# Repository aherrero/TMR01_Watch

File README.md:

# TMR01_Watch
Digital homemade wrist watch - Bora Watch

https://aherrero.github.io/atmega328/rtc/clock/diy/2018/11/29/BoraWatchv2.html

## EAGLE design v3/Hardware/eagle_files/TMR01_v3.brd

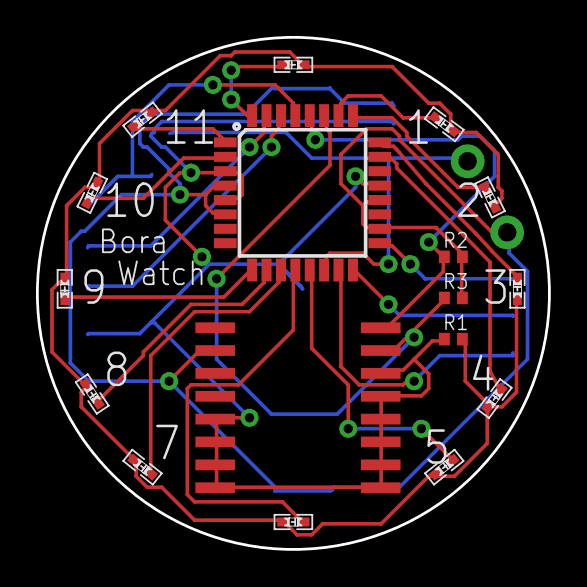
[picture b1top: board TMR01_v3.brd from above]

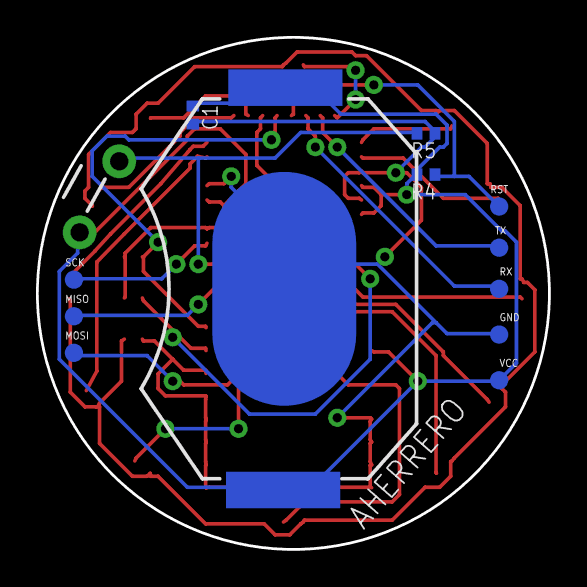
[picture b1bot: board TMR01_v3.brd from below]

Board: 2 copper layers, 28.4 x 28.4 mm, 30 parts (13 on the bottom side), 24 nets.

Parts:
BT1: BATTCON_20MM_4LEGS
C1: 100nF; 0402
D1, D2, D3, D4, D5, D6, D7, D8, D9, D10, D11, D12: 0402.LED
IC1: DS3231/SO; SO16W
R1: 470; 0402
R2, R3, R4, R5: 10k; 0402
S1: MOMENTARY-SWITCH-SPST; TACTILE_SWITCH_PTH_2_AHE
TP3, TP4, TP7, TP8, TP9, TP10, TP11, TP12: TEST-POINT3X4; PAD.03X.04
U1: ATMEGA328P_TQFP; TQFP32-08

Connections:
D1: D1.P$1, U1.26
D2: D2.P$1, U1.25
D3: D3.P$1, U1.24
D4: D4.P$1, U1.23
D5: D5.P$1, U1.13
D6: D6.P$1, U1.12
D7: D7.P$1, U1.11
D8: D8.P$1, U1.10
D9: D9.P$1, U1.9
D10: D10.P$1, U1.2
D11: D11.P$1, U1.1
D12: D12.P$1, U1.32
GND: BT1.NEGATIVE, C1.2, IC1.5, IC1.6, IC1.7, IC1.8, IC1.9, IC1.10, IC1.11, IC1.12, IC1.13, IC1.14, R1.1, R5.1, TP12.P$1, U1.3, U1.5, U1.21
MISO: TP7.P$1, U1.16
MOSI: TP10.P$1, U1.15
unnamed: D1.P$2, D2.P$2, D3.P$2, D4.P$2, D5.P$2, D6.P$2, D7.P$2, D8.P$2, D9.P$2, D10.P$2, D11.P$2, D12.P$2, R1.2
RST: R4.1, TP11.P$1, U1.29
RX: TP3.P$1, U1.30
SCK: TP9.P$1, U1.17
SCL: IC1.16, R2.1, U1.28
SDA: IC1.15, R3.1, U1.27
SS: R5.2, S1.2, U1.14
TX: TP4.P$1, U1.31
VCC: BT1.POSITIVE@1, BT1.POSITIVE@2, BT1.POSITIVE@3, BT1.POSITIVE@4, C1.1, IC1.2, R2.2, R3.2, R4.2, S1.1, TP8.P$1, U1.4, U1.6, U1.18, U1.20

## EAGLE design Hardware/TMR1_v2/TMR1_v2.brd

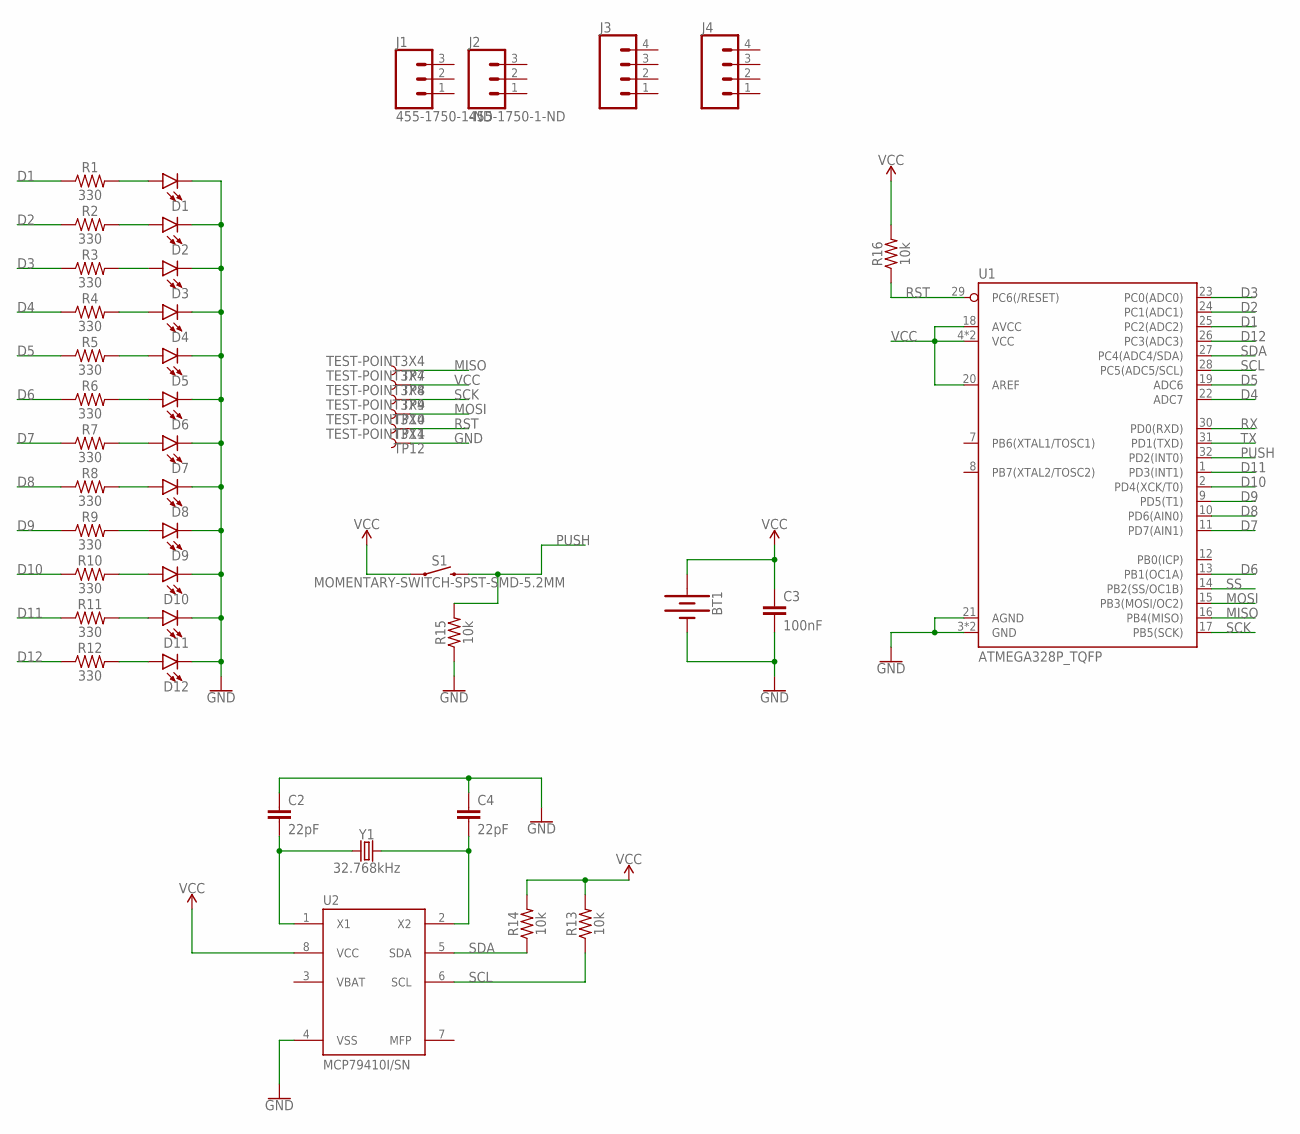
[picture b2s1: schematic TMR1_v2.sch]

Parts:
BT1: BATTERY-20MM_SMD_4LEGS; BATTCON_20MM_4LEGS
C2, C4: 22pF; 0603
C3: 100nF; 0603
D1, D2, D3, D4, D5, D6, D7, D8, D9, D10, D11, D12: LED0603; LED-0603
J1, J2: 455-1750-1-ND; 1X03
J3, J4: CONN_04; 1X04
R1, R2, R3, R4, R5, R6, R7, R8, R9, R10, R11, R12: 330; 0603
R13, R14, R15, R16: 10k; 0603
S1: MOMENTARY-SWITCH-SPST-SMD-5.2MM; TACTILE_SWITCH_SMD_5.2MM
TP7, TP8, TP9, TP10, TP11, TP12: TEST-POINT3X4; PAD.03X.04
U1: ATMEGA328P_TQFP; TQFP32-08
U2: MCP79410I/SN; SO8
Y1: 32.768kHz; CRYSTAL-SMD-MC-146

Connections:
D1: R1.1, U1.25 (PC2(ADC2))
D2: R2.1, U1.24 (PC1(ADC1))
D3: R3.1, U1.23 (PC0(ADC0))
D4: R4.1, U1.22 (ADC7)
D5: R5.1, U1.19 (ADC6)
D6: R6.1, U1.13 (PB1(OC1A))
D7: R7.1, U1.11 (PD7(AIN1))
D8: R8.1, U1.10 (PD6(AIN0))
D9: R9.1, U1.9 (PD5(T1))
D10: R10.1, U1.2 (PD4(XCK/T0))
D11: R11.1, U1.1 (PD3(INT1))
D12: R12.1, U1.26 (PC3(ADC3))
GND: BT1.NEGATIVE (-), C2.1, C3.2, C4.1, D1.C, D2.C, D3.C, D4.C, D5.C, D6.C, D7.C, D8.C, D9.C, D10.C, D11.C, D12.C, R15.1, TP12.P$1, U1.3 (GND), U1.5 (GND), U1.21 (AGND), U2.4 (VSS)
MISO: TP7.P$1, U1.16 (PB4(MISO))
MOSI: TP10.P$1, U1.15 (PB3(MOSI/OC2))
unnamed: D8.A, R8.2
unnamed: D7.A, R7.2
unnamed: D6.A, R6.2
unnamed: D5.A, R5.2
unnamed: D4.A, R4.2
unnamed: D3.A, R3.2
unnamed: D2.A, R2.2
unnamed: D1.A, R1.2
unnamed: C2.2, U2.1 (X1), Y1.P$2 (1)
unnamed: C4.2, U2.2 (X2), Y1.P$1 (2)
unnamed: D9.A, R9.2
unnamed: D10.A, R10.2
unnamed: D11.A, R11.2
unnamed: D12.A, R12.2
PUSH: R15.2, S1.3 (2), U1.32 (PD2(INT0))
RST: R16.1, TP11.P$1, U1.29 (PC6(/RESET))
RX: U1.30 (PD0(RXD))
SCK: TP9.P$1, U1.17 (PB5(SCK))
SCL: R13.1, U1.28 (PC5(ADC5/SCL)), U2.6 (SCL)
SDA: R14.1, U1.27 (PC4(ADC4/SDA)), U2.5 (SDA)
SS: U1.14 (PB2(SS/OC1B))
TX: U1.31 (PD1(TXD))
VBAT: U2.3 (VBAT)
VCC: BT1.POSITIVE@1 (+), BT1.POSITIVE@2 (+), BT1.POSITIVE@3 (+), BT1.POSITIVE@4 (+), C3.1, R13.2, R14.2, R16.2, S1.1, TP8.P$1, U1.4 (VCC), U1.6 (VCC), U1.18 (AVCC), U1.20 (AREF), U2.8 (VCC)

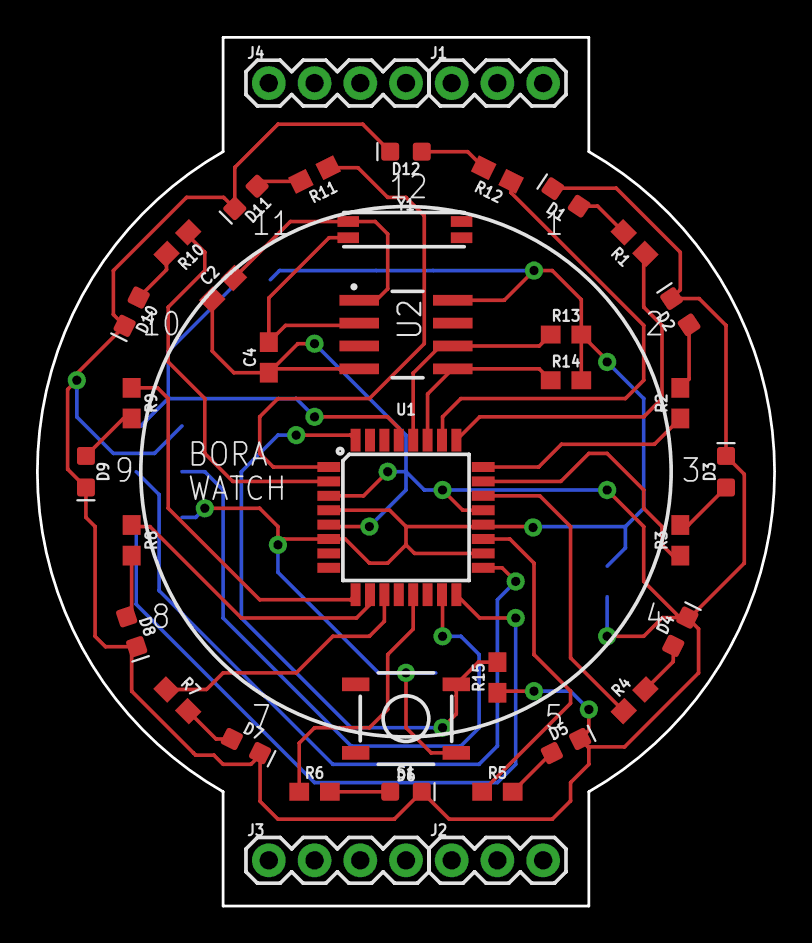
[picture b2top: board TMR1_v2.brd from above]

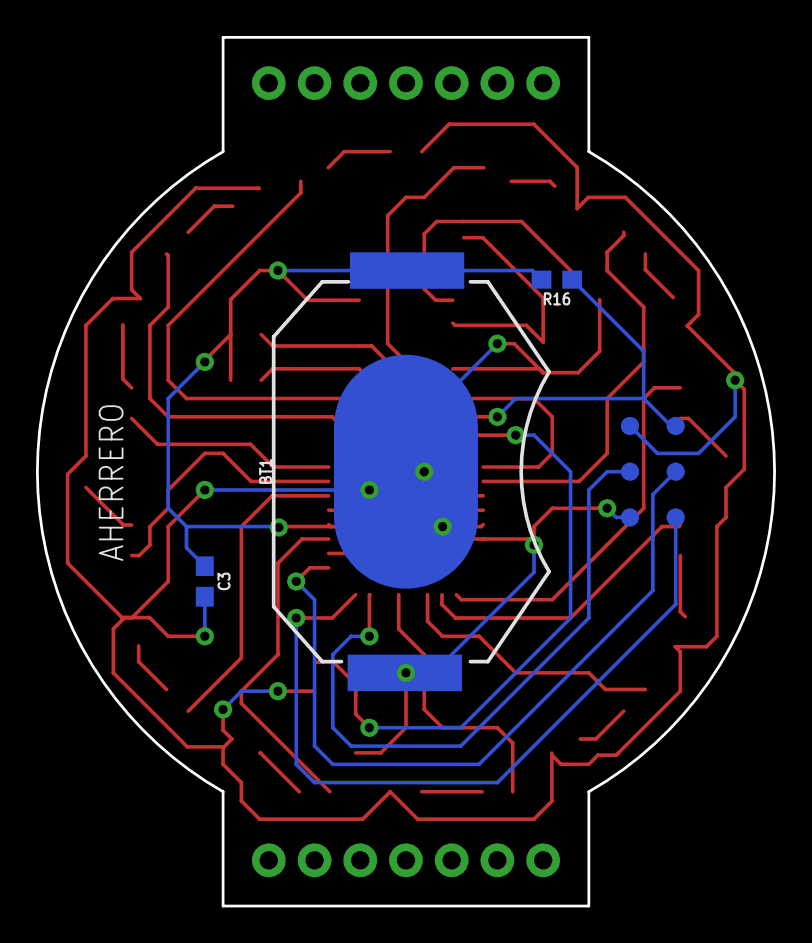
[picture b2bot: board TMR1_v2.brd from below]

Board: 2 copper layers, 41.0 x 48.3 mm, 46 parts (9 on the bottom side), 35 nets.

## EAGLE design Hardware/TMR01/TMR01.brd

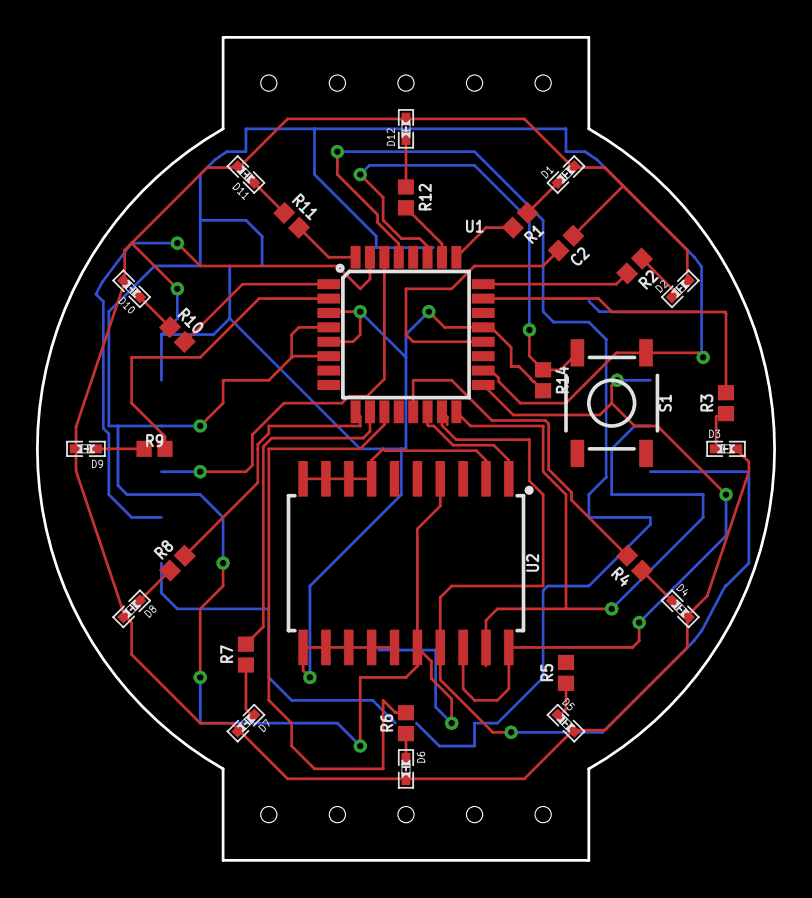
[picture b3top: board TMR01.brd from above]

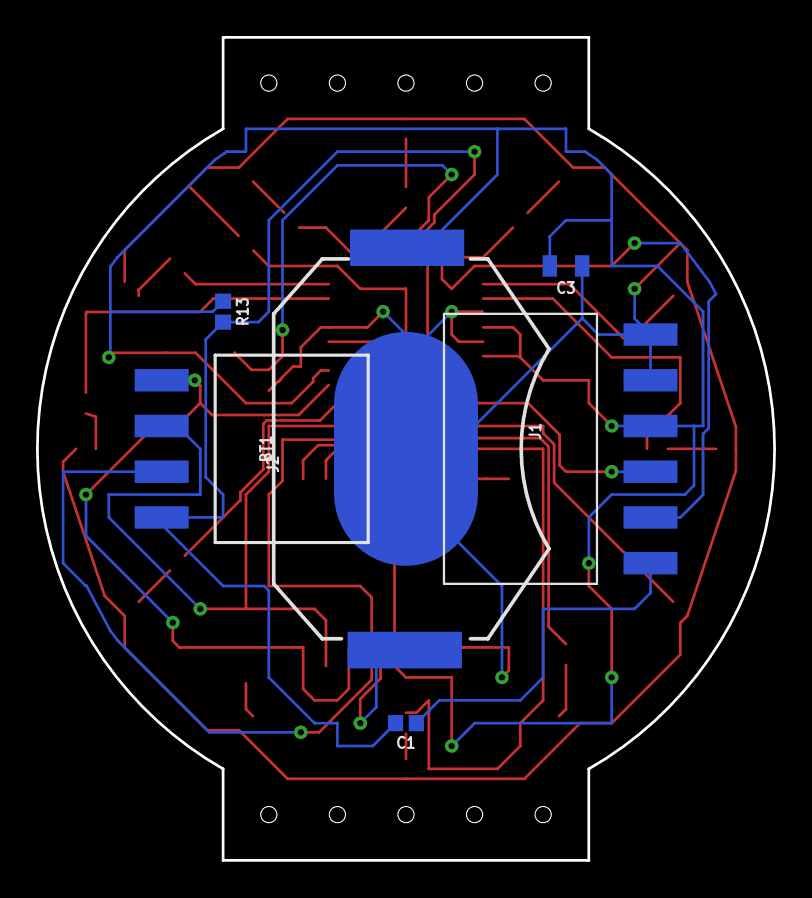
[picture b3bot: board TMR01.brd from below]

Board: 2 copper layers, 41.0 x 45.7 mm, 36 parts (6 on the bottom side), 36 nets.

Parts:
BT1: BATTCON_20MM_4LEGS
C1, C2: 0.1uF; 0402
C3: 10uF; 0805
D1, D2, D3, D4, D5, D6, D7, D8, D9, D10, D11, D12: 0402.LED
FRAME1: FRAME-LETTER; CREATIVE_COMMONS
J1: 1X06-SMD-FEMALE
J2: 1X04_SMD_RA_FEMALE
R1, R2, R3, R4, R5, R6, R7, R8, R9, R10, R11, R12: 200; 0402
R13, R14: 10k; 0402
S1: MOMENTARY-SWITCH-SPST-SMD-5.2MM; TACTILE_SWITCH_SMD_5.2MM
U1: ATMEGA328P_TQFP; TQFP32-08
U2: DS3234; SO20-0.3

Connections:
D1: R11.2, U1.32
D2: R10.2, U1.1
D3: R9.2, U1.2
D4: R8.2, U1.9
D5: R7.2, U1.10
D6: R6.2, U1.11
D7: R5.2, U1.12
D8: R4.2, U1.13
D9: R3.2, U1.23
D10: R2.2, U1.24
D11: R1.2, U1.25
D12: R12.2, U1.26
DTR: C1.1, J1.1
GND: BT1.NEGATIVE, C2.1, C3.1, D1.P$2, D2.P$2, D3.P$2, D4.P$2, D5.P$2, D6.P$2, D7.P$2, D8.P$2, D9.P$2, D10.P$2, D11.P$2, D12.P$2, J1.5, J1.6, R14.2, U1.3, U1.5, U1.21, U2.2, U2.7, U2.8, U2.9, U2.10, U2.11, U2.12, U2.13, U2.14, U2.15
MISO: J2.3, U1.16, U2.19
MOSI: J2.2, U1.15, U2.17
unnamed: D8.P$1, R8.1
unnamed: D7.P$1, R7.1
unnamed: D6.P$1, R6.1
unnamed: D5.P$1, R5.1
unnamed: D4.P$1, R4.1
unnamed: D3.P$1, R3.1
unnamed: D2.P$1, R2.1
unnamed: D1.P$1, R1.1
unnamed: C2.2, U1.20
unnamed: D9.P$1, R9.1
unnamed: D10.P$1, R10.1
unnamed: D11.P$1, R11.1
unnamed: D12.P$1, R12.1
PUSH: R14.1, S1.3, U1.27
RST: C1.2, J2.1, R13.2, U1.29
RX: J1.3, U1.30
SCK: J2.4, U1.17, U2.18, U2.20
SS: U1.14, U2.1
TX: J1.2, U1.31
VCC: BT1.POSITIVE@1, BT1.POSITIVE@2, BT1.POSITIVE@3, BT1.POSITIVE@4, C3.2, J1.4, R13.1, S1.1, U1.4, U1.6, U1.18, U2.4, U2.16

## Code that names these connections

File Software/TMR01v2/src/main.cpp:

#include <Arduino.h>

// External libraries
#include "MCP7940.h"
#include "LowPower.h"

// Internal Libraries
#include "ClockLeds.h"

// Constant
const int BUTTON_PIN = 2;    // Button For interruption (PD2, INT0, atmega 32)

const int LED12_PIN = A3;   //PC3, atmega 26
const int LED1_PIN  = A2;   //PC2, atmega 25
const int LED2_PIN  = A1;   //PC1, atmega 24
const int LED3_PIN  = A0;   //PC0, atmega 23

const int LED4_PIN  = 13;   // Originally to A7 (D4_NA). But change to SCK -> PB5 (Arduino13). Atmega 17
const int LED5_PIN  = 12;   // Originally to A6 (D5_NA). But change to MISO -> PB4. Atmega 16

const int LED6_PIN  = 9;    //PB1, atmega 13

const int LED7_PIN  = 7;    //PD7, atmega 11
const int LED8_PIN  = 6;    //PD6, atmega 10
const int LED9_PIN  = 5;    //PD5, atmega 9
const int LED10_PIN = 4;    //PD4, atmega 2
const int LED11_PIN = 3;    //PD3, atmega 1

int ALL_LEDS_PIN[] = {LED12_PIN, LED1_PIN, LED2_PIN,
                        LED3_PIN, LED4_PIN, LED5_PIN,
                        LED6_PIN, LED7_PIN, LED8_PIN,
                        LED9_PIN, LED10_PIN, LED11_PIN};

const int WATCH_MODE_TIME = 0;
const int WATCH_MODE_SET_HOUR = 1;
const int WATCH_MODE_SET_MIN = 2;

// Variables
MCP7940_Class MCP7940;
ClockLeds clockLeds(ALL_LEDS_PIN);

int BORA_WATCH_MODE = WATCH_MODE_TIME;

DateTime time_now;

// Button detection long press
long longPressTime = 1000;

volatile int buttonPressed = 0;
unsigned long startMillis = 0;
unsigned long currentsMillis = 0;

const int SHORT_PRESSED = 1;
const int LONG_PRESSED = 2;

/*
* Return 1 if short pressed (Default < 1s)
* Return 2 if long pressed (Default > 1s) but still pressed
* Return 0 on other case
*/
int calculateLongShortButton()
{
    int resultLongPress = 0;
    unsigned long diffMillis = currentsMillis - startMillis;

    if(buttonPressed == 1 && diffMillis < longPressTime)
    {
        // Starting acum
        currentsMillis = millis();
    }
    else
    {
        if(diffMillis > 5)
        {
            if(diffMillis > longPressTime)
            {
                resultLongPress = LONG_PRESSED;
            }
            else
            {
                resultLongPress = SHORT_PRESSED;
            }
        }

        startMillis = millis();
        currentsMillis = millis();
    }

    return resultLongPress;
}


// callback
void wakeUp()
{
    // Just a handler for the pin interrupt.
}

void pin_ISR()
{
    if(digitalRead(BUTTON_PIN) == HIGH)
        buttonPressed = 1;
    else
        buttonPressed = 0;
}

// Setup

void setup()
{
    // Leds output
    for(int i=0; i< sizeof(ALL_LEDS_PIN);i++)
        pinMode(ALL_LEDS_PIN[i], OUTPUT);

    // Button input
    pinMode(BUTTON_PIN, INPUT);

    // RTC
    while (!MCP7940.begin())
    {
        // Unable to find MCP7940M. Checking again in 3s.
        delay(3000);
    }

    // MCP7940 initialized

    while (!MCP7940.deviceStatus())
    {
        // Oscillator is off, turning it on
        bool deviceStatus = MCP7940.deviceStart();
        if (!deviceStatus)
        {
            // Oscillator did not start, trying again.
            delay(1000);
        }
    }

    //MCP7940.adjust();   // Adjust time with the compilation time
    MCP7940.adjust(DateTime(2000,1,1,9,36,0));   //Set a specific time
    delay(1000);

    // Good configuration
    clockLeds.SequenceLeds(50);

    // Attach an interrupt to the ISR vector (long or short press)
    attachInterrupt(0, pin_ISR, CHANGE);
}

void loop()
{
    int resultLongPress = 0;

    switch (BORA_WATCH_MODE)
    {
        case WATCH_MODE_TIME:
            // Disable external pin interrupt for counting time
            detachInterrupt(0);
            delay(10);

            // Allow wake up pin to trigger interrupt on low.
            attachInterrupt(0, wakeUp, HIGH);

            // Enter power down state with ADC and BOD module disabled.
            // Wake up when wake up pin is low.
            LowPower.powerDown(SLEEP_FOREVER, ADC_OFF, BOD_OFF);

            // Disable external pin interrupt on wake up pin.
            detachInterrupt(0);
            delay(10);

            // Do something here after wake up until next loop to sleep

            // Show the time
            // get time from RTC
            time_now = MCP7940.now();
            //  now.year(), now.month(), now.day(), now.hour(), now.minute(), now.second()

            // Display
            // if hour = minutes
            // only the minutes blinking
            clockLeds.DisplayHourLed(time_now.hour());
            for(int i = 0; i < 3; i++)
            {
                // blinking 1s, 3 times
                clockLeds.DisplayMinutesBlinking(time_now.minute(), 500);

                // If the button continue pressed (after showing time at least once (1s after)
                if(digitalRead(BUTTON_PIN) == HIGH)
                {
                    // Set the hour
                    BORA_WATCH_MODE = WATCH_MODE_SET_HOUR;
                    clockLeds.SequenceLeds(50);

                    calculateLongShortButton(); //Restart variables once unpressed
                    // Attach an interrupt to the ISR vector
                    attachInterrupt(0, pin_ISR, CHANGE);

                    break;  //Break the loop for showing time
                }
            }
        break;

        case WATCH_MODE_SET_HOUR:
            // Clean Leds
            clockLeds.PowerOffAllLeds();

            // Get the hour
            time_now = MCP7940.now();
            //Normally minutes blink each 1 sec. IN setting time, the hours blink each 500ms
            clockLeds.DisplayHourBlinking(time_now.hour(), 100);

            // Read button status and long/short press
            resultLongPress = calculateLongShortButton();
            if(resultLongPress == SHORT_PRESSED)
            {
                DateTime newtime(time_now.year(),time_now.month(),time_now.day(),
                                time_now.hour() + 1,time_now.minute(),time_now.second());

                MCP7940.adjust(newtime);   //Set a specific time
            }
            else if(resultLongPress == LONG_PRESSED)
            {
                // Set the minutes
                BORA_WATCH_MODE = WATCH_MODE_SET_MIN;
                clockLeds.SequenceLeds(50);
                calculateLongShortButton(); //Restart variables once unpressed

            }


        break;

        case WATCH_MODE_SET_MIN:
            // Clean Leds
            clockLeds.PowerOffAllLeds();

            // Get the hour
            time_now = MCP7940.now();
            //Normally minutes blink each 1 sec. IN setting time, the minutes blink each 500ms
            clockLeds.DisplayMinutesBlinking(time_now.minute(), 50);

            // Read button status and long/short press
            resultLongPress = calculateLongShortButton();
            if(resultLongPress == SHORT_PRESSED)
            {
                // +5 if we set each 5 minutes and display each 5 minutes
                DateTime newtime(time_now.year(),time_now.month(),time_now.day(),
                                time_now.hour(),time_now.minute() + 5,time_now.second());

                MCP7940.adjust(newtime);   //Set a specific time
            }
            else if(resultLongPress == LONG_PRESSED)
            {
                // Come back show time
                BORA_WATCH_MODE = WATCH_MODE_TIME;
                clockLeds.SequenceLeds(25);
                clockLeds.SequenceLeds(25);
                calculateLongShortButton(); //Restart variables once unpressed
            }


        break;
    }   //end switch

    clockLeds.PowerOffAllLeds();
}   //end loop

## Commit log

2018-10-30 Initial TMR01 v2 - eagle schematics
2018-11-01 Board created with a watch layout
2018-11-01 connecting grounds and vcc with via
2018-11-01 everything except D7
2018-11-01 Ratsnest – Nothing To Do!
2018-11-06 HW after route evertything and having 300 errors. Looking for another solution
2018-11-07 HW changed to easy RTC. Starting SW testing
2018-11-09 HW: new redesign testing. SW: main.cpp with RTC and sleep mode testing
2018-11-12 HW modifications trying to fit the bora watch.\nSoftware trying the RTC low power version, and atmega with shift register and RTC (possible wall watch)
2018-11-12 Shift register with random values for outputs. Improvement of wall watch
2018-11-12 std easy schematic with all elements in board before route
2018-11-12 before routing
2018-11-14 we may not need RX and TX
2018-11-14 PCB finished and Gerbers generated
2018-11-16 testing display: counter instead hhmm
2018-11-18 moved testing SW to new project wall clock
2018-11-18 Starting SW for new board TMR01v2
2018-11-20 state machine for the watch, with long and short press implemented
2018-11-22 Setting and display the minutes correctly
2018-11-29 correction for the analogic pings ADC6-7 with MISO-SCK, HW and SW
2018-12-04 Modify long press button with interrupt
2018-12-04 fixed problems with button interruption
2019-01-10 git ignore correctly
2019-02-13 different folders for the version. we need the version in the repository instead of tags in order to access pdf and raw data directly for the links
2019-02-20 new design v3, smaller and rtc ds3231
2019-02-25 fixed sda scl in rtc
2019-03-04 pins output modified, not using miso mosi connected to leds
2019-03-19 gerbers generated
2019-03-19 0402 leds possible wrong footprint. Changed temporaly by resistors footprint
2019-03-29 modified gerbers
2019-04-08 recover status with leds
2019-04-08 added screenshot png

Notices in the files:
parts and their libraries:
SparkFun-Batteries: Licensing: Creative Commons ShareAlike 4.0 International - https://creativecommons.org/licenses/by-sa/4.0
SparkFun-Aesthetics: Released under the Creative Commons Attribution Share-Alike 4.0 License
SparkFun-Aesthetics: https://creativecommons.org/licenses/by-sa/4.0
